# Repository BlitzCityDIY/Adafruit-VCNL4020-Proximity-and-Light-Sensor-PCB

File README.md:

## Adafruit VCNL4020 Proximity and Light Sensor - STEMMA QT / Qwiic PCB

<a href="http://www.adafruit.com/products/5810"><br/>
Click here to purchase one from the Adafruit shop</a>

PCB files for the Adafruit VCNL4020 Proximity and Light Sensor - STEMMA QT / Qwiic. 

Format is EagleCAD schematic and board layout
* https://www.adafruit.com/product/5810

### Description

The VCNL4020 is a handy two-in-one sensor, with a proximity sensor that works from 0 to 200mm (about 7.5 inches) and light sensor with range of 0.26 to 16,000 lux.

We've all been there. That thing is close but how close? When you need to measure a small distance with reasonable accuracy, such as the rough height of particularly calm bumble bee, the VCNL4020 Proximity Sensor from Vishay can do that for you. If perchance you also needed to measure the amount of light at the same time, perhaps to let the bee to know if it's time for bed, you're in luck! The VCNL4020 can do that too (bumble bee not included, we tried putting it in the anti-static bag but it started buzzing in a threatening manner).

This sensor is similar to the VCNL4040 but with a wider light sensor range, up to 16000 lux!

As with all of our new I2C sensors, we've taken the VCNL4020 and put it onto a breakout PCB along with support circuitry to let you use this little wonder with 3.3V (Feather/Raspberry Pi) or 5V (Arduino/ Metro328) logic levels. Since it speaks I2C you can easily connect it up with two wires (plus power and ground!).  We've even included SparkFun qwiic compatible STEMMA QT connectors for the I2C bus so you don't even need to solder! Just wire up to your favorite micro and you can use our Arduino drivers to easily interface with the VCNL4020 and make approximate approximations of proximity in no time! 

QT Cable is not included, but we have a variety in the shop. 

The VCNL4020 comes with a variety of knobs you can tweak, such as how many samples per second (a.k.a the integration time between measurements) - more samples per second means faster results but not as good at measuring low level light. With 16-bit light level reports, and 0.25 lux per bit, you can measure from 0.25 to 16,000 lux! And various averaging filters can do your low-pass filtering for you  so you get less spiky results. However, there is no other sensitivity/integration time controls.

### License

Adafruit invests time and resources providing this open source design, please support Adafruit and open-source hardware by purchasing products from [Adafruit](https://www.adafruit.com)!

Designed by Limor Fried/Ladyada for Adafruit Industries.

Creative Commons Attribution/Share-Alike, all text above must be included in any redistribution. 
See license.txt for additional details.

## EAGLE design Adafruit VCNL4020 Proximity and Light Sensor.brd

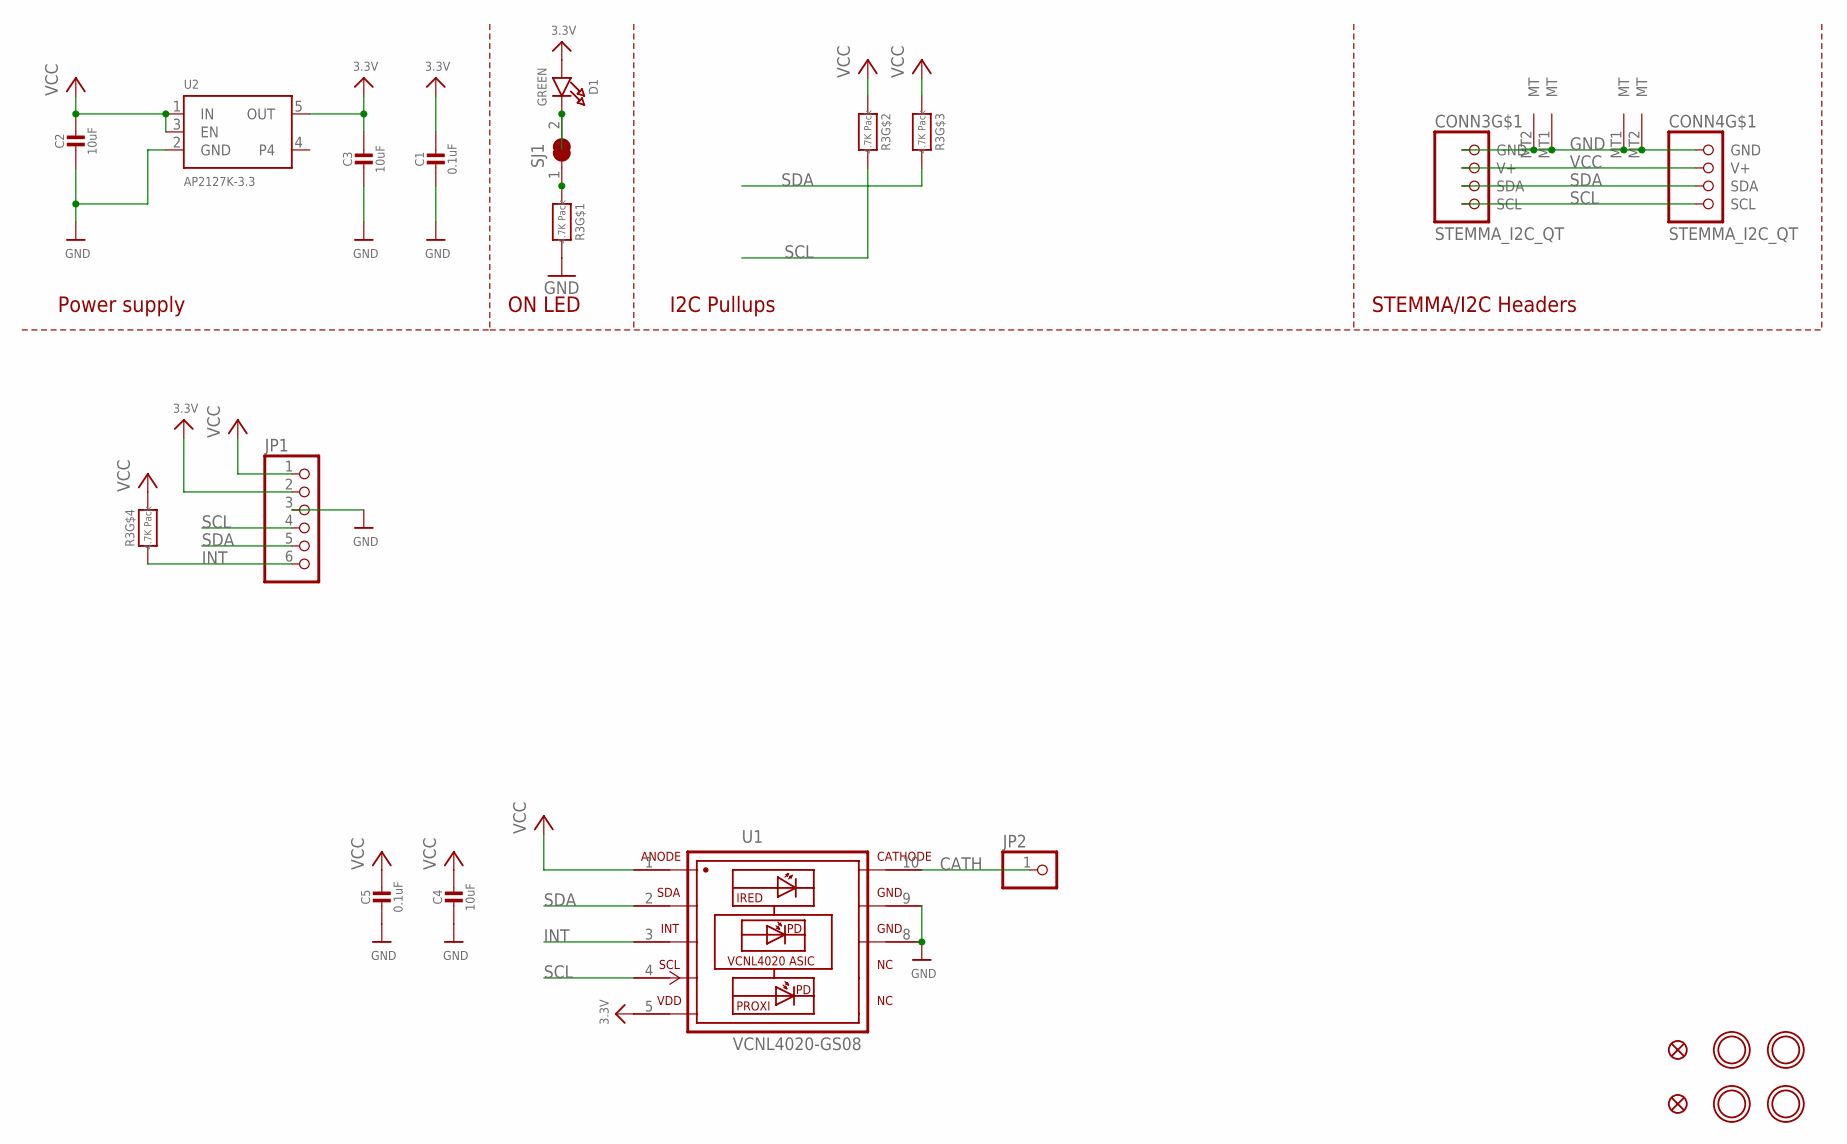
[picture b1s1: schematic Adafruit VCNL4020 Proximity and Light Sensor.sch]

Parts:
C1, C5: 0.1uF; 0603-NO
C2, C3, C4: 10uF; 0805-NO
CONN3, CONN4: STEMMA_I2C_QT; JST_SH4
D1: GREEN; CHIPLED_0603_NOOUTLINE
FID3, FID4: FIDUCIAL_1MM
JP1: HEADER-1X670MIL; 1X06_ROUND_70
JP2: HEADER-1X1ROUND; 1X01_ROUND
R3: 4.7K Pack; RESPACK_4X0603
SJ1: SOLDERJUMPER_CLOSED; SOLDERJUMPER_CLOSEDWIRE
U1: VCNL4020-GS08; PHODET_VCNL4020
U2: AP2127K-3.3; SOT23-5
U$1, U$17, U$19, U$21: MOUNTINGHOLE2.5; MOUNTINGHOLE_2.5_PLATED

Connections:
3.3V: C1.1, C3.1, D1.A, JP1.2, U1.5 (VDD), U2.5 (OUT)
CATH: JP2.1, U1.10 (IR-CATHODE)
GND: C1.2, C2.2, C3.2, C4.2, C5.2, CONN3.1 (GND), CONN3.MT1 (MT), CONN3.MT2 (MT), CONN4.1 (GND), CONN4.MT1 (MT), CONN4.MT2 (MT), JP1.3, R3.8 (2), U1.8 (GND2), U1.9 (GND), U2.2 (GND)
INT: JP1.6, R3.4 (1), U1.3 (INT)
unnamed: D1.C, SJ1.2
unnamed: R3.1, SJ1.1
SCL: CONN3.4 (SCL), CONN4.4 (SCL), JP1.4, R3.7 (2), U1.4 (SCL)
SDA: CONN3.3 (SDA), CONN4.3 (SDA), JP1.5, R3.6 (2), U1.2 (SDA)
VCC: C2.1, C4.1, C5.1, CONN3.2 (V+), CONN4.2 (V+), JP1.1, R3.2 (1), R3.3 (1), R3.5 (2), U1.1 (IR-ANODE), U2.1 (IN), U2.3 (EN)

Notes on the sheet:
I2C Pullups
STEMMA/I2C Headers
ON LED
Power supply

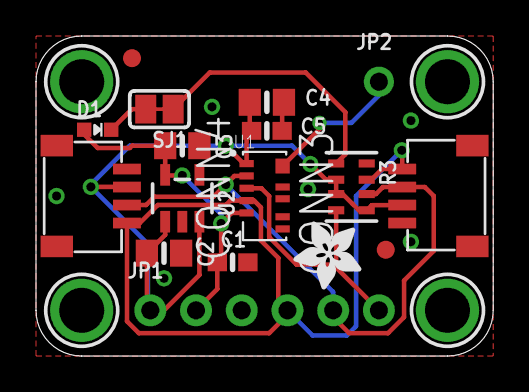
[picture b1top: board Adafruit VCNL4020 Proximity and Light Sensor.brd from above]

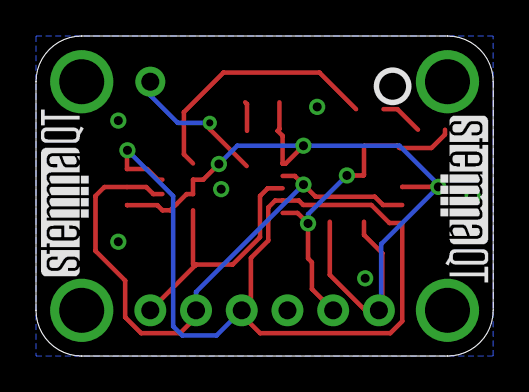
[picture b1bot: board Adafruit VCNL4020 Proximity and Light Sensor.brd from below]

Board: 2 copper layers, 25.4 x 17.8 mm, 36 parts (6 on the bottom side), 9 nets.

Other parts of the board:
PLABEL0: PLABEL0
PLABEL1: PLABEL1
PLABEL2: PLABEL2
PLABEL3: PLABEL3
PLABEL4: PLABEL4
PLABEL5: PLABEL5
PLABEL7: PLABEL7
PLABEL8: PLABEL8
PLABEL10: PLABEL10
PLABEL11: PLABEL11
PLABEL12: PLABEL12
PLABEL13: PLABEL13
U$22: ADAFRUIT_3.5MM
U$25: PCBFEAT-REV-040
U$30, U$31: STEMMAQT

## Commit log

2023-10-06 adding cookiecutter output

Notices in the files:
parts and their libraries:
microbuilder: This work is placed in the public domain, and may be freely used for commercial and non-commercial work with the following conditions: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
